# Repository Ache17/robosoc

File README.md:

# Quala

### Description
The goal of the project is to create an open drone that could be used potentially in future for running future project. Some initial idea was to create a drone swarm ( smaller drones "scouters" and larger drones "tankers", [Alex's pitch text needed for that]). Overall we want to have: 
- an OK performance mechanics ( we got the good donations and have stuff from DJI ), 
- own flight controller ( or at least ported by us to ardupilot in order to understand it better and modify our system in future)
- Video processing, communication and streaming done on raspberry pi ( open source, easy to modify, used in university courses)
- Control ( or sending command) done by Laptop

### System Diagram :

## Components :
- Frame : [DJI F450](https://www.unmannedtechshop.co.uk/product/f450-quadcopter-frame-with-integrated-pdb/) 
- Autopilot : [Ardupilot](https://ardupilot.org/)
- ESCs : [E300](https://www.dji.com/uk/e300) (used now) or [XXD 30A](https://uk.banggood.com/Wholesale-XXD-HW30A-30A-Brushless-Motor-ESC-For-Airplane-Quadcopter-p-50621.html?utm_source=googleshopping&utm_medium=cpc_organic&gmcCountry=GB&utm_content=minha&utm_campaign=minha-gbg-en-pc&currency=GBP&cur_warehouse=CN&createTmp=1&utm_source=googleshopping&utm_medium=cpc_us&utm_content=jeff&utm_campaign=jeff-co-pla-all-11sale-uk-211021&ad_id=554630521428&gclid=CjwKCAjwrqqSBhBbEiwAlQeqGvUba-68dGHQIvDt9tkU8KaKOyWThmB51lSY50i6YMVbNij9YVvPQBoCxCkQAvD_BwE) ( just because of cheap, maybe utilized in future)
- Motors : DJI 2212 motor 920kv ( standard DJI motors that came with the motors)
- Controller : Designed by us Board with stm32f411 or stm32h745/755 
- Video Processing / Communication (WiFi) : [Raspberry pi 4b](https://www.raspberrypi.com/products/raspberry-pi-4-model-b/) or [Pi Zero W 2](https://www.raspberrypi.com/products/raspberry-pi-zero-2-w/)
- Battery : [Tattu 4S 3700mAh](https://www.unmannedtechshop.co.uk/product/tattu-3700mah-45c-4s1p-lipo/)
- GPS : ( link needed ) 
- IMU : [MPU6050](https://invensense.tdk.com/products/motion-tracking/6-axis/mpu-6050/) ( support for drivers from Ardupilot), or [ISM330](https://estore.st.com/en/ism330dhcxtr-cpn.html) (high performance, not supprted by Ardupilot, plan to add it to our design )
- Pressure Sensor : [BMP280](https://www.bosch-sensortec.com/products/environmental-sensors/pressure-sensors/bmp280/) (stanadard pressure sensor)
- Power Distribution Board : Used by the one on DJI or this [one](https://www.unmannedtechshop.co.uk/product/power-distribution-board-with-led-voltage-regulator/)

### Autopilot + controller
Goal is to familliarize ourselves with [Ardupilot](https://ardupilot.org/) autopilot ( very good, active, great community and open project) so that we can contribute further to it. We wanted to designed custom controller for it. Due to lack of components we settled for black-pill board ( with stm32f411. There is a problem with flash size that is 512kB, ardupilot requires much more). 

We designed also controller on which we can place directly the microcontroller ( to avoid flash size issues, we can place stm32f405 or stm32h755)

Communication between flight controller and raspberry pi is as described [here](https://ardupilot.org/dev/docs/raspberry-pi-via-mavlink.html).

### Video streaming
normally it requires video data streaming protocol (.h264 or .h265). Unfortunately we weren't able to achieve good results on it ( very high latency) so we settled for motion-jpeg streaming with low resolutions. 

### Theoretical evaluation 
Theoretical evaluation of the design was done on [flyeval.com](flyeval.com) ( [Introduction to Multicopter Design and Control, Quan Quan 2017](https://link.springer.com/book/10.1007/978-981-10-3382-7) ) and the screenshots below are taken from that website. 

#### Performance of Model

#### Mathematical model of design

### pics from picture
(components, not yet working)

### Ardupilot notes: 
Sparky2, speedybeef4, SuccexF4, VRBrain-v51,
[17:33]
Compatible IMUs :
[17:35]
BMI055, BMI088, BMI160, BMI270, MPU6000, MPU9250,  ICM20608, ICM20602, ICM20601, ICM20789, ICM20689,  ICM20948, ICM20648 and ICM20649, ICM-40609, ICM-42688, ICM-42605, ICM-40605, IIM-42652, L3G4200D, LSM9DS0, LSM9DS1,
[17:39]
Compatible PRessure : BMP085, BMP280, BMP388, DPS280, FBM320, ICM20789, LPS2XH, MS5611,  SPL06
[17:42]
GPS : NMEA, NOVA, SBF, SBP, SBP2, SIRF, UAVCAN, UBLOX, RTCM3

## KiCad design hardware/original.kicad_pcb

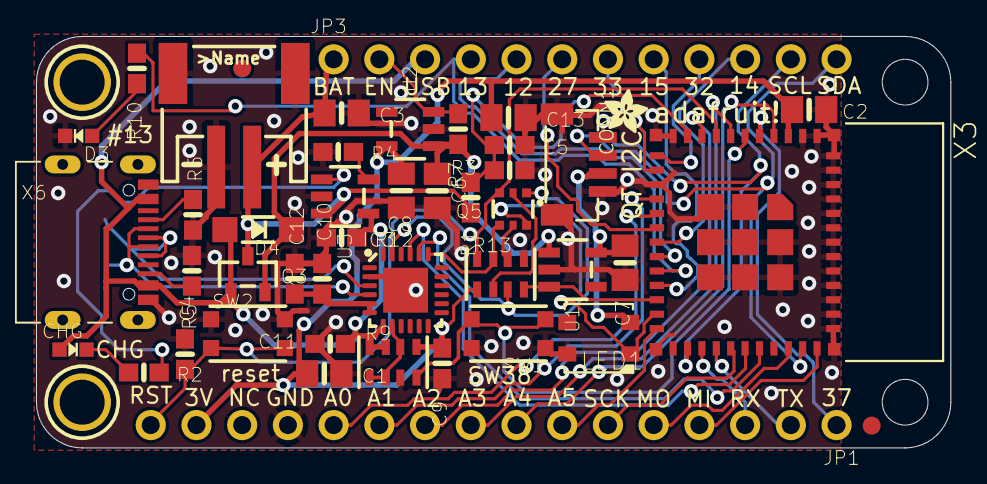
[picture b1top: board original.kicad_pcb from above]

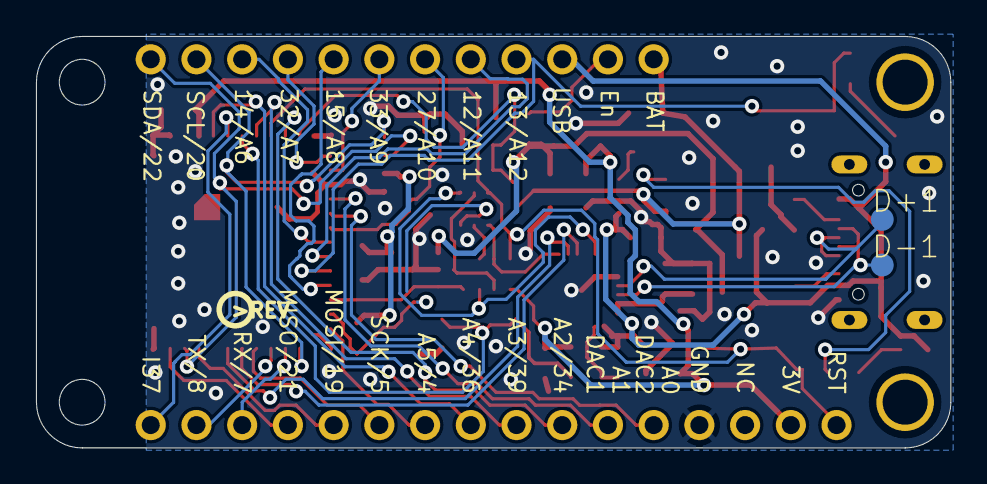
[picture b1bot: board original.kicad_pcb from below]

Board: 2 copper layers, 50.8 x 22.9 mm, 52 parts (3 on the bottom side), 49 nets.

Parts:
@HOLE0, @HOLE1: (no value)
C1, C2, C13: 10uF; 0805-NO
C3, C6, C7, C8: 10µF; 0805-NO
C4, C5, C9, C10: 1uF; 0603-NO
C11, C12: 0.1uF; 0603-NO
CHG: ORANGE; CHIPLED_0603_NOOUTLINE
CONN1: STEMMA_I2C_QTRA; JST_SH4_RA
D3: RED; CHIPLED_0603_NOOUTLINE
D4: MBR540; SOD-123
D+1: TPB1,27; B1,27
D-1: TPB1,27; B1,27
IC3: CP2102N-24; QFN24_4MM_SMSC
JP1: 1X16_ROUND
JP3: 1X12_ROUND
LED1: WS2812B3535; LED3535
Q3: DMG3415U; SOT23-R
Q5: DUAL NPN; SOT363
R1, R3: 200K; 0603-NO
R2, R4, R5, R6, R10: 5.1K; 0603-NO
R7, R12: 100K; 0603-NO
R9: 47K; RESPACK_4X0603
R13: 10K; RESPACK_4X0603
SW1, SW2: KMR2; BTN_KMR2_4.6X2.8
U1, U2: AP2112-3.3; SOT23-5
U3: MCP73831T-2ACI/OT; SOT23-5
U$13: PCBFEAT-REV-040
U$14: ADAFRUIT_2.5MM
U$31, U$32: MOUNTINGHOLE2.5; MOUNTINGHOLE_2.5_PLATED
U$34, U$35: FIDUCIAL_1MM
X1: JSTPH; JSTPH2_BATT
X3: ESP32-PICO-MINI-02MINI; ESP32-PICO-MINI
X6: USB Type C; USB_C_CUSB31-CFM2AX-01-X

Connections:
3.3V: C1.1, C2.1, C8.1, C9.1, C13.1, JP1.15, R9.5, R13.1, U2.5, X3.3
3.45V: C10.1, C12.1, IC3.5, IC3.6
A0_DAC2: JP1.12, X3.16
A1_DAC1: JP1.11, X3.15
A2_I34: JP1.10, X3.9
A3_I39: JP1.9, X3.7
A4_I36: JP1.8, X3.4
A5_IO4: JP1.7, X3.24
A13_I35: C5.1, R1.1, R3.2, X3.10
CC1: R6.2, X6.A5
CC2: R5.2, X6.B5
D+: D+1.TP, IC3.3, X6.A6, X6.B6
D-: D-1.TP, IC3.4, X6.A7, X6.B7
DTR: IC3.23, Q5.1, R13.3
EN: JP3.2, R7.1, U2.3
GND: C1.2, C2.2, C3.2, C4.2, C5.2, C6.2, C7.2, C8.2, C9.2, C10.2, C11.2, C12.2, C13.2, CONN1.1, CONN1.MT1, CONN1.MT2, D3.C, IC3.2, IC3.THERM, JP1.13, LED1.4, R3.1, R4.1, R5.1, R6.1, R9.3, R12.1, R13.5, SW1.A, SW1.A', SW2.A, SW2.A', U1.2, U2.2, U3.2, X1.1, X1.NC1, X1.NC2, X3.1, X3.2, X3.11, X3.14, X3.36, X3.37, X3.38, X3.39, X3.40, X3.41, X3.42, X3.43, X3.44, X3.45, X3.46, X3.47, X3.48, X3.49, X3.50, X3.51, X3.52, X3.53, X3.54, X3.55, X3.56, X3.57, X3.58, X3.59, X3.60, X3.61, X6.A1B12, X6.B1A12
GPIO0: LED1.1, Q5.6, X3.23
I37: JP1.1, X3.5
IO12_A11: JP3.5, X3.19
IO13_A12: JP3.4, R10.1, X3.20
IO14_A6: JP3.10, X3.18
IO15_A8: JP3.8, X3.21
IO27_A10: JP3.6, X3.17
IO32_A7: JP3.9, X3.12
IO33_A9: JP3.7, X3.13
MISO: JP1.4, X3.35
MOSI: JP1.5, X3.33
unnamed: CHG.C, R2.1
unnamed: R2.2, U3.1
unnamed: R4.2, U3.5
unnamed: D3.A, R10.2
unnamed: R9.4, SW1.B, SW1.B', X3.6
unnamed: Q5.5, R13.6
unnamed: Q5.2, R13.2
NEOI2C_PWR: R13.4, U1.3, X3.22
RTS: IC3.19, Q5.4, R13.7
RX/IO7: JP1.3, X3.27
RXD0: IC3.21, X3.30
SCK: JP1.6, X3.29
SCL: CONN1.4, JP3.11, X3.26
SDA: CONN1.3, JP3.12, X3.34
TX/IO8: JP1.2, X3.28
TXD0: IC3.20, X3.31
VBAT: C3.1, JP3.1, Q3.3, R1.2, U3.3, X1.2
VBUS: C11.1, CHG.A, D4.A, IC3.7, JP3.3, Q3.1, R9.7, R9.8, R12.2, U3.4, X6.A4B9, X6.B4A9
VBUS_DET: IC3.8, R9.1, R9.2, R9.6
VHI: C6.1, D4.C, Q3.2, R7.2, U1.1, U2.1
V_NEOI2C: C7.1, CONN1.2, LED1.2, U1.5
~RESET: C4.1, JP1.16, Q5.3, R13.8, SW2.B, SW2.B', X3.8

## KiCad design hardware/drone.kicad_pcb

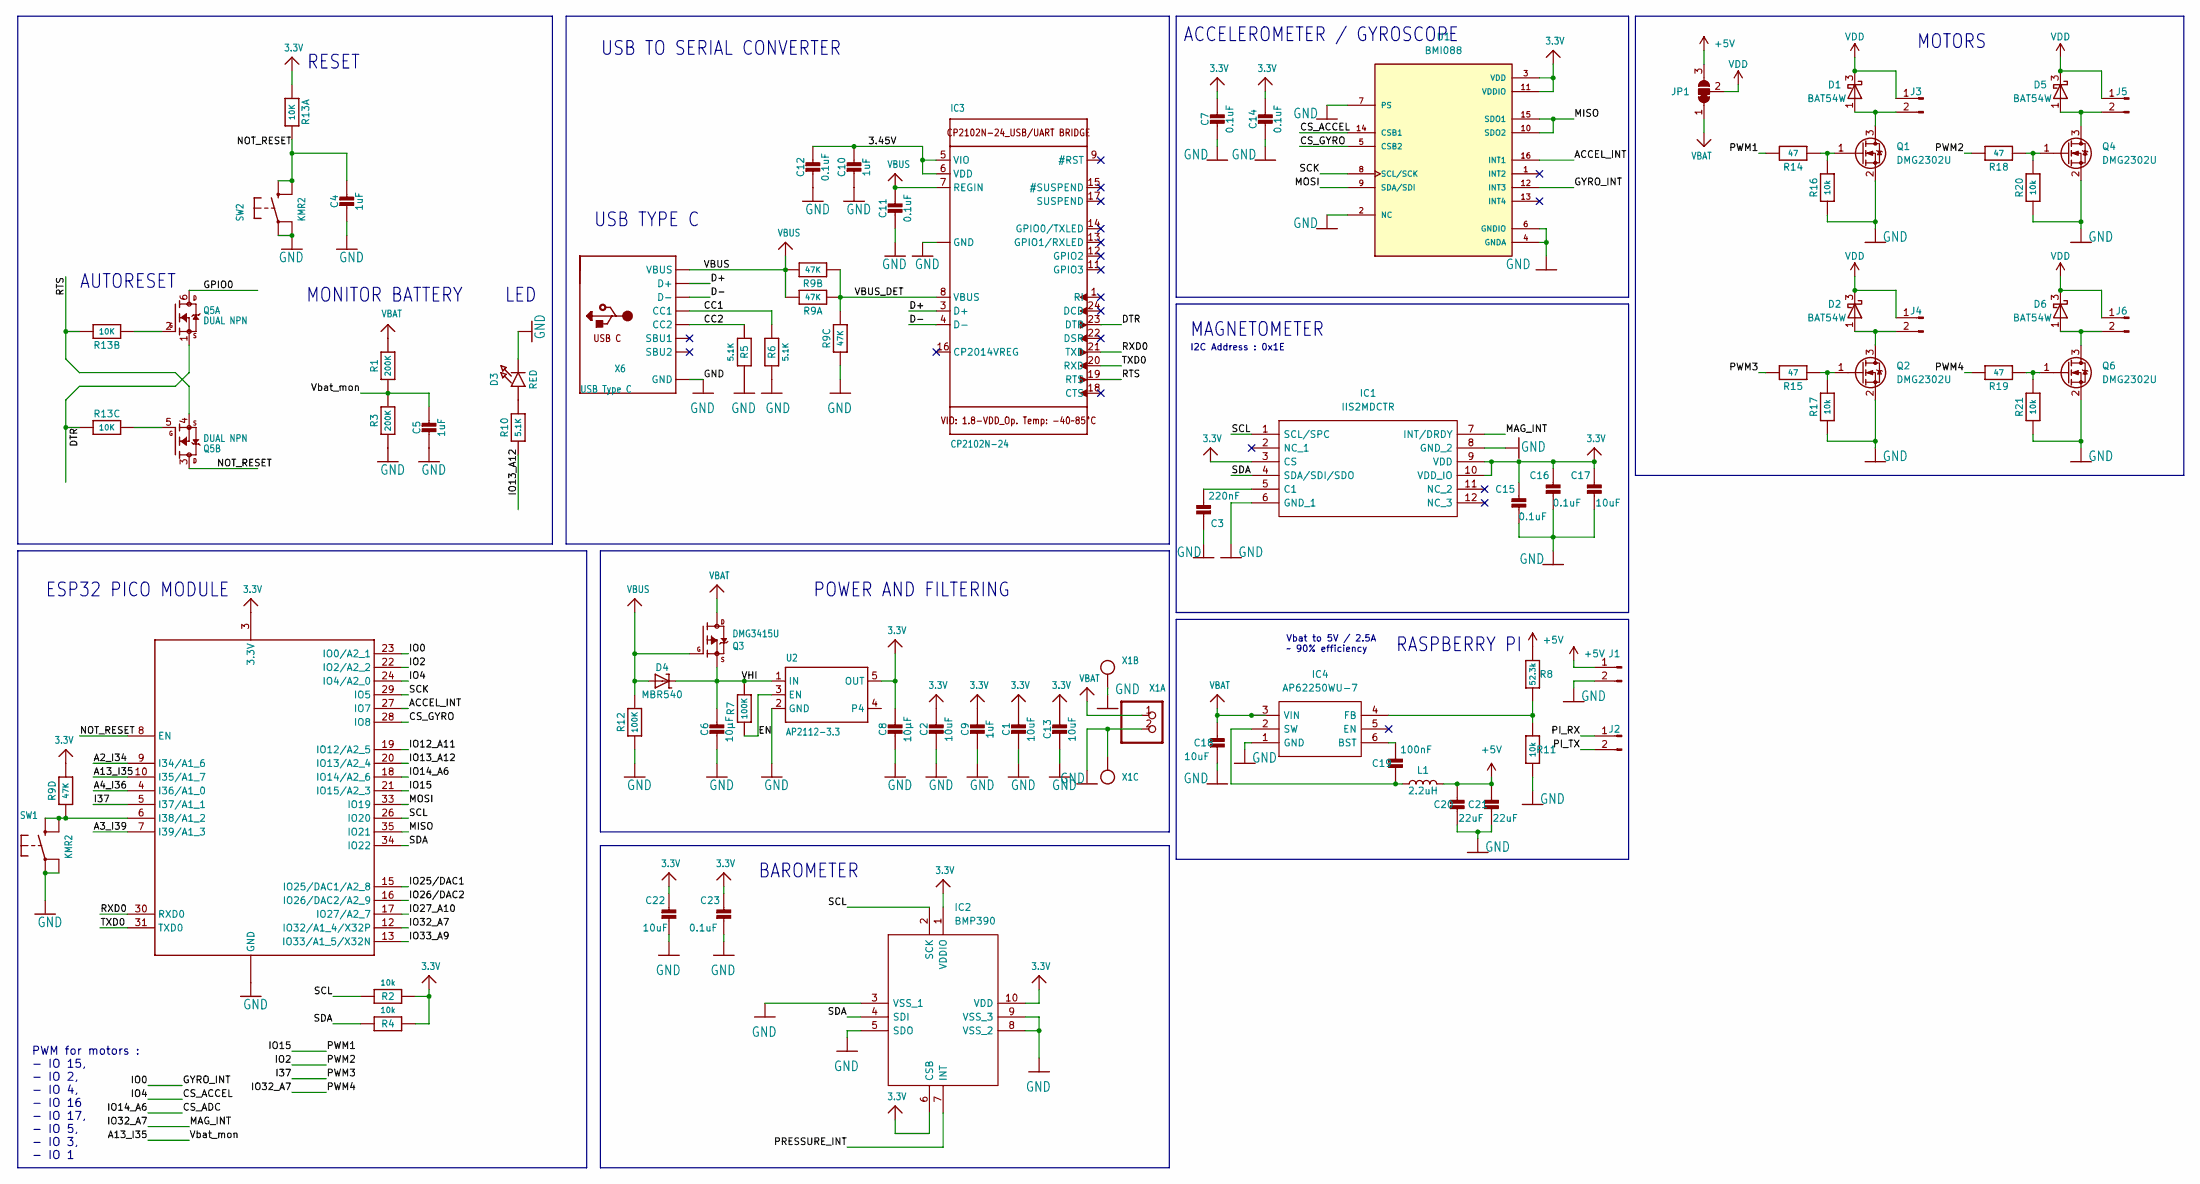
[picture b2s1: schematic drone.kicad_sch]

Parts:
C1, C2, C13: 10uF; 0805-NO
C3: 220nF; 0603-NO
C4, C5, C9, C10: 1uF; 0603-NO
C6: 10µF; 0805-NO
C7, C11, C12, C14, C15, C16, C23: 0.1uF; 0603-NO
C8: F; 0805-NO
C17, C18, C22: 10uF; 0603-NO
C19: 100nF; 0603-NO
C20, C21: 22uF; 0603-NO
D1, D2, D5, D6: BAT54W; SOT-323_SC-70
D3: RED; CHIPLED_0603_NOOUTLINE
D4: MBR540; SOD-123
IC1: IIS2MDCTR; Manufacturer_Part_Number IIS2MDCTR; Mouser Part Number 511-IIS2MDCTR
IC2: BMP390; Manufacturer_Part_Number BMP390; Mouser Part Number 262-BMP390
IC3: CP2102N-24; QFN24_4MM_SMSC
IC4: AP62250WU-7; SOT95P280X100-6N; Manufacturer_Part_Number AP62250WU-7; Mouser Part Number 621-AP62250WU-7
J1, J2, J3, J4, J5, J6: Conn_01x02_Male; conn_01x02
JP1: SolderJumper_3_Bridged12; SolderJumper-3_P1.3mm_Bridged12_RoundedPad1.0x1.5mm_NumberL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
L1: 2.2uH; L_1812_4532Metric
Q1, Q2, Q4, Q6: DMG2302U; SOT-23
Q3: DMG3415U; SOT23-R
Q5: DUAL NPN; SOT363
R1, R3: 200K; 0603-NO
R2, R4, R11, R16, R17, R20, R21: 10k; 0603-NO
R5, R6, R10: 5.1K; 0603-NO
R7, R12: 100K; 0603-NO
R8: 52.3k; 0603-NO
R9: 47K; RESPACK_4X0603
R13: 10K; RESPACK_4X0603
R14, R15, R18, R19: 47; 0603-NO
SW1, SW2: KMR2; BTN_KMR2_4.6X2.8
U1: BMI088; PQFN50P450X300X100-16N
U2: AP2112-3.3; SOT23-5
X1: CON_JST_PH_2PIN_MTPH2; JSTPH2_BATT
X3: ESP32-PICO-MINI-02MINI; ESP32-PICO-MINI
X6: USB Type C; USB_C_CUSB31-CFM2AX-01-X

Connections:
3.3V: C1.1, C2.1, C7.1, C8.1, C9.1, C13.1, C14.1, C15.1, C16.1, C17.1, C22.1, C23.1, IC1.3 (CS), IC1.9 (VDD), IC1.10 (VDD_IO), IC2.1 (VDDIO), IC2.6 (CSB), IC2.10 (VDD), R2.1, R4.1, R9.5 (2), R13.1, U1.3 (VDD), U1.11 (VDDIO), U2.5 (OUT), X3.3 (3.3V)
+5V: C20.1, C21.1, J1.1, JP1.3 (B), L1.2, R8.2
/3.45V: C10.1, C12.1, IC3.5 (VIO), IC3.6 (VDD)
/A2_I34: X3.9 (I34/A1_6)
/A3_I39: X3.7 (I39/A1_3)
/A4_I36: X3.4 (I36/A1_0)
/A13_I35: C5.1, R1.1, R3.2, X3.10 (I35/A1_7)
/ACCEL_INT: U1.16 (INT1), X3.27 (IO7)
/CC1: R6.2, X6.A5 (CC1)
/CC2: R5.2, X6.B5 (CC2)
/CS_ACCEL: U1.14 (CSB1), X3.24 (IO4/A2_0)
/CS_ADC: X3.18 (IO14/A2_6)
/CS_GYRO: U1.5 (CSB2), X3.28 (IO8)
/D+: IC3.3 (D+), X6.A6 (D+), X6.B6 (D+)
/D-: IC3.4 (D-), X6.A7 (D-), X6.B7 (D-)
/DTR: IC3.23 (DTR), Q5.1 (S), R13.3 (1)
/EN: R7.1, U2.3 (EN)
/GPIO0: Q5.6 (D)
/GYRO_INT: U1.12 (INT3), X3.23 (IO0/A2_1)
/IO12_A11: X3.19 (IO12/A2_5)
/IO13_A12: R10.1, X3.20 (IO13/A2_4)
/IO25/DAC1: X3.15 (IO25/DAC1/A2_8)
/IO26/DAC2: X3.16 (IO26/DAC2/A2_9)
/IO27_A10: X3.17 (IO27/A2_7)
/IO33_A9: X3.13 (IO33/A1_5/X32N)
/MISO: U1.10 (SDO2), U1.15 (SDO1), X3.35 (IO21)
/MOSI: U1.9 (SDA/SDI), X3.33 (IO19)
/NOT_RESET: C4.1, Q5.3 (D), R13.8 (2), SW2.B (S), SW2.B' (S1), X3.8 (EN)
/PI_RX: J2.1
/PI_TX: J2.2
/PRESSURE_INT: IC2.7 (INT)
/PWM1: R14.2, X3.21 (IO15/A2_3)
/PWM2: R18.2, X3.22 (IO2/A2_2)
/PWM3: R15.2, X3.5 (I37/A1_1)
/PWM4: IC1.7 (INT/DRDY), R19.2, X3.12 (IO32/A1_4/X32P)
/RTS: IC3.19 (RTS), Q5.4 (S), R13.7 (2)
/RXD0: IC3.21 (TXD), X3.30 (RXD0)
/SCK: U1.8 (SCL/SCK), X3.29 (IO5)
/SCL: IC1.1 (SCL/SPC), IC2.2 (SCK), R2.2, X3.26 (IO20)
/SDA: IC1.4 (SDA/SDI/SDO), IC2.4 (SDI), R4.2, X3.34 (IO22)
/TXD0: IC3.20 (RXD), X3.31 (TXD0)
/VBUS_DET: IC3.8 (VBUS), R9.1, R9.2 (1), R9.6 (2)
/VHI: C6.1, D4.C, Q3.2 (S), R7.2, U2.1 (IN)
GND: C1.2, C2.2, C3.1, C4.2, C5.2, C6.2, C7.2, C8.2, C9.2, C10.2, C11.2, C12.2, C13.2, C14.2, C15.2, C16.2, C17.2, C18.2, C20.2, C21.2, C22.2, C23.2, D3.C, IC1.6 (GND_1), IC1.8 (GND_2), IC2.3 (VSS_1), IC2.5 (SDO), IC2.8 (VSS_2), IC2.9 (VSS_3), IC3.2 (GND), IC3.THERM (GND), IC4.1 (GND), J1.2, Q1.2 (S), Q2.2 (S), Q4.2 (S), Q6.2 (S), R3.1, R5.1, R6.1, R9.3 (1), R11.1, R12.1, R16.1, R17.1, R20.1, R21.1, SW1.A, SW1.A' (P1), SW2.A, SW2.A' (P1), U1.2 (NC), U1.4 (GNDA), U1.6 (GNDIO), U1.7 (PS), U2.2 (GND), X1.2, X1.NC1, X1.NC2, X3.1 (GND), X3.2 (GND), X3.11 (GND), X3.14 (GND), X3.36 (GND), X3.37 (GND), X3.38 (GND), X3.39 (GND), X3.40 (GND), X3.41 (GND), X3.42 (GND), X3.43 (GND), X3.44 (GND), X3.45 (GND), X3.46 (GND), X3.47 (GND), X3.48 (GND), X3.49 (GND), X3.50 (GND), X3.51 (GND), X3.52 (GND), X3.53 (GND), X3.54 (GND), X3.55 (GND), X3.56 (GND), X3.57 (GND), X3.58 (GND), X3.59 (GND), X3.60 (GND), X3.61 (GND), X6.A1B12 (GND), X6.B1A12 (GND)
unnamed: C3.2, IC1.5 (C1)
unnamed: C19.1, IC4.6 (BST)
unnamed: C19.2, IC4.2 (SW), L1.1
unnamed: D1.1 (A), J3.2, Q1.3 (D)
unnamed: D2.1 (A), J4.2, Q2.3 (D)
unnamed: D3.A, R10.2
unnamed: D5.1 (A), J5.2, Q4.3 (D)
unnamed: D6.1 (A), J6.2, Q6.3 (D)
unnamed: IC4.4 (FB), R8.1, R11.2
unnamed: Q1.1 (G), R14.1, R16.2
unnamed: Q2.1 (G), R15.1, R17.2
unnamed: Q4.1 (G), R18.1, R20.2
unnamed: Q5.2 (G), R13.2 (1)
unnamed: Q5.5 (G), R13.6 (2)
unnamed: Q6.1 (G), R19.1, R21.2
unnamed: R9.4 (1), SW1.B (S), SW1.B' (S1), X3.6 (I38/A1_2)
VBAT: C18.1, IC4.3 (VIN), JP1.1 (A), Q3.3 (D), R1.2, X1.1
VBUS: C11.1, D4.A, IC3.7 (REGIN), Q3.1 (G), R9.7 (2), R9.8 (2), R12.2, X6.A4B9 (VBUS), X6.B4A9 (VBUS)
VDD: D1.3 (K), D2.3 (K), D5.3 (K), D6.3 (K), J3.1, J4.1, J5.1, J6.1, JP1.2 (C)

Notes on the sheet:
ACCELEROMETER / GYROSCOPE
USB TO SERIAL CONVERTER
MOTORS
AUTORESET
USB TYPE C
RASPBERRY PI
PWM for motors : - IO 15, - IO 2, - IO 4, - IO 16 - IO 17, - IO 5, - IO 3, - IO 1
MAGNETOMETER
BAROMETER
MONITOR BATTERY
POWER AND FILTERING
I2C Address : 0x1E
RESET
ESP32 PICO MODULE
LED
Vbat to 5V / 2.5A ~ 90% efficiency

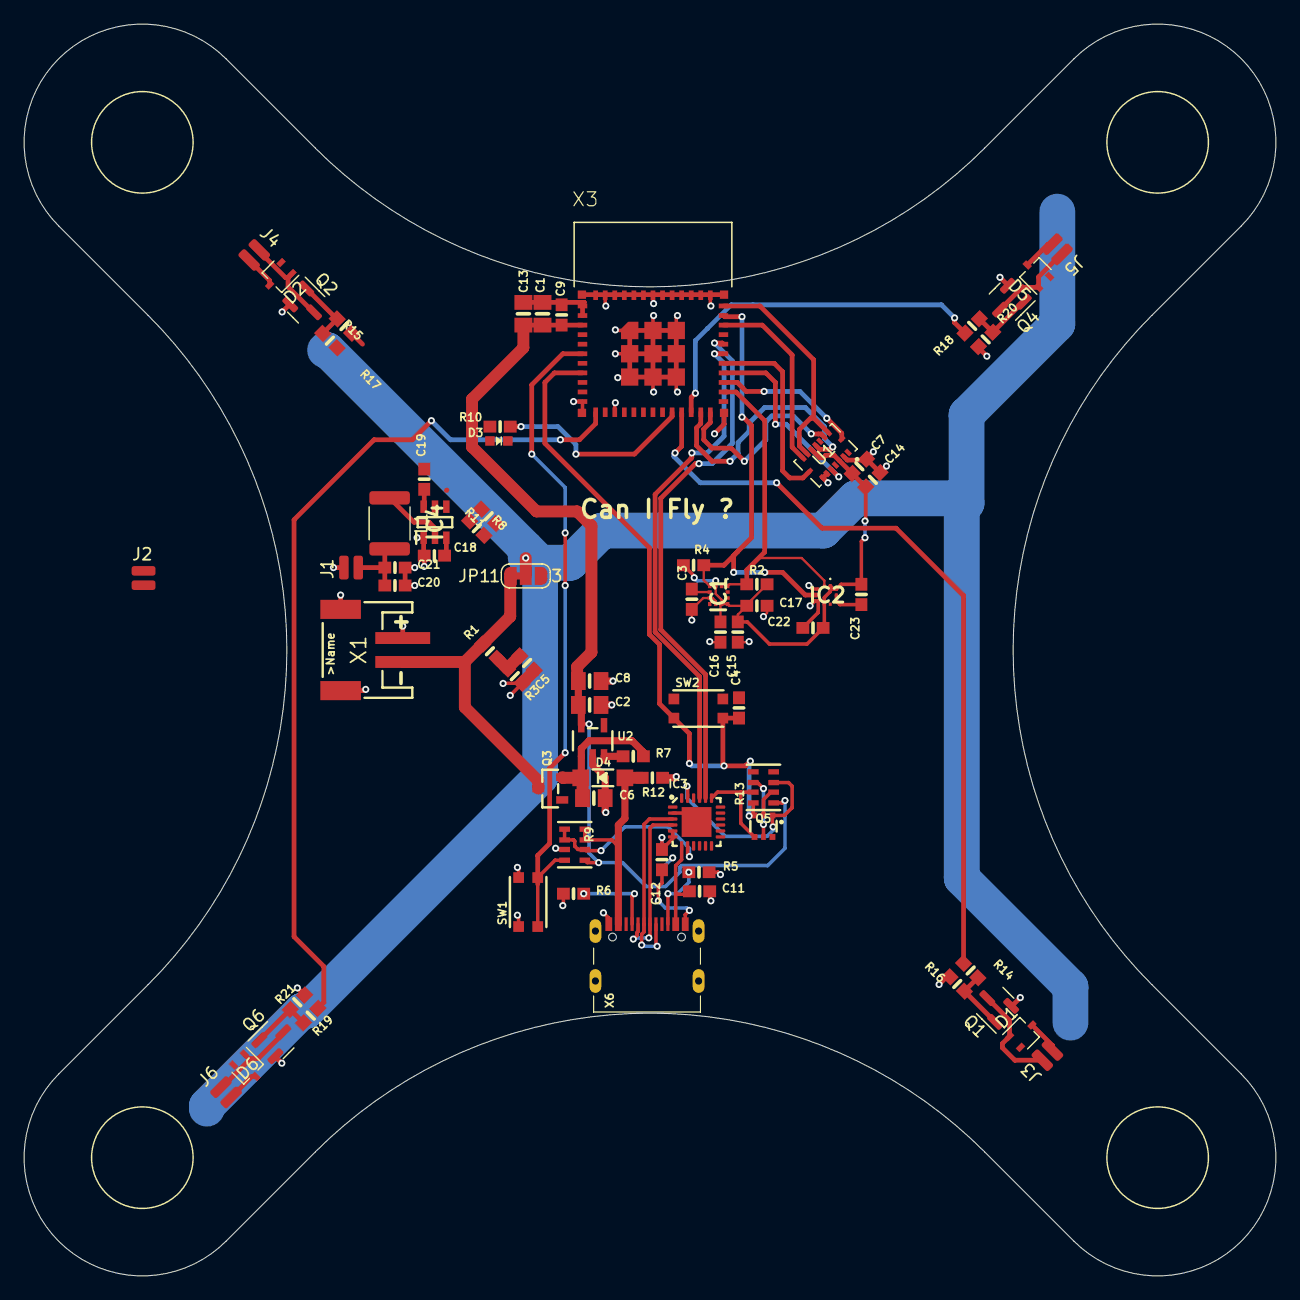
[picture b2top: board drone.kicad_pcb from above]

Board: 2 copper layers, 104.8 x 104.8 mm, 75 parts (1 on the bottom side), 50 nets.

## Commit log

2022-04-04 propaganda
2022-12-05 hardware v1
